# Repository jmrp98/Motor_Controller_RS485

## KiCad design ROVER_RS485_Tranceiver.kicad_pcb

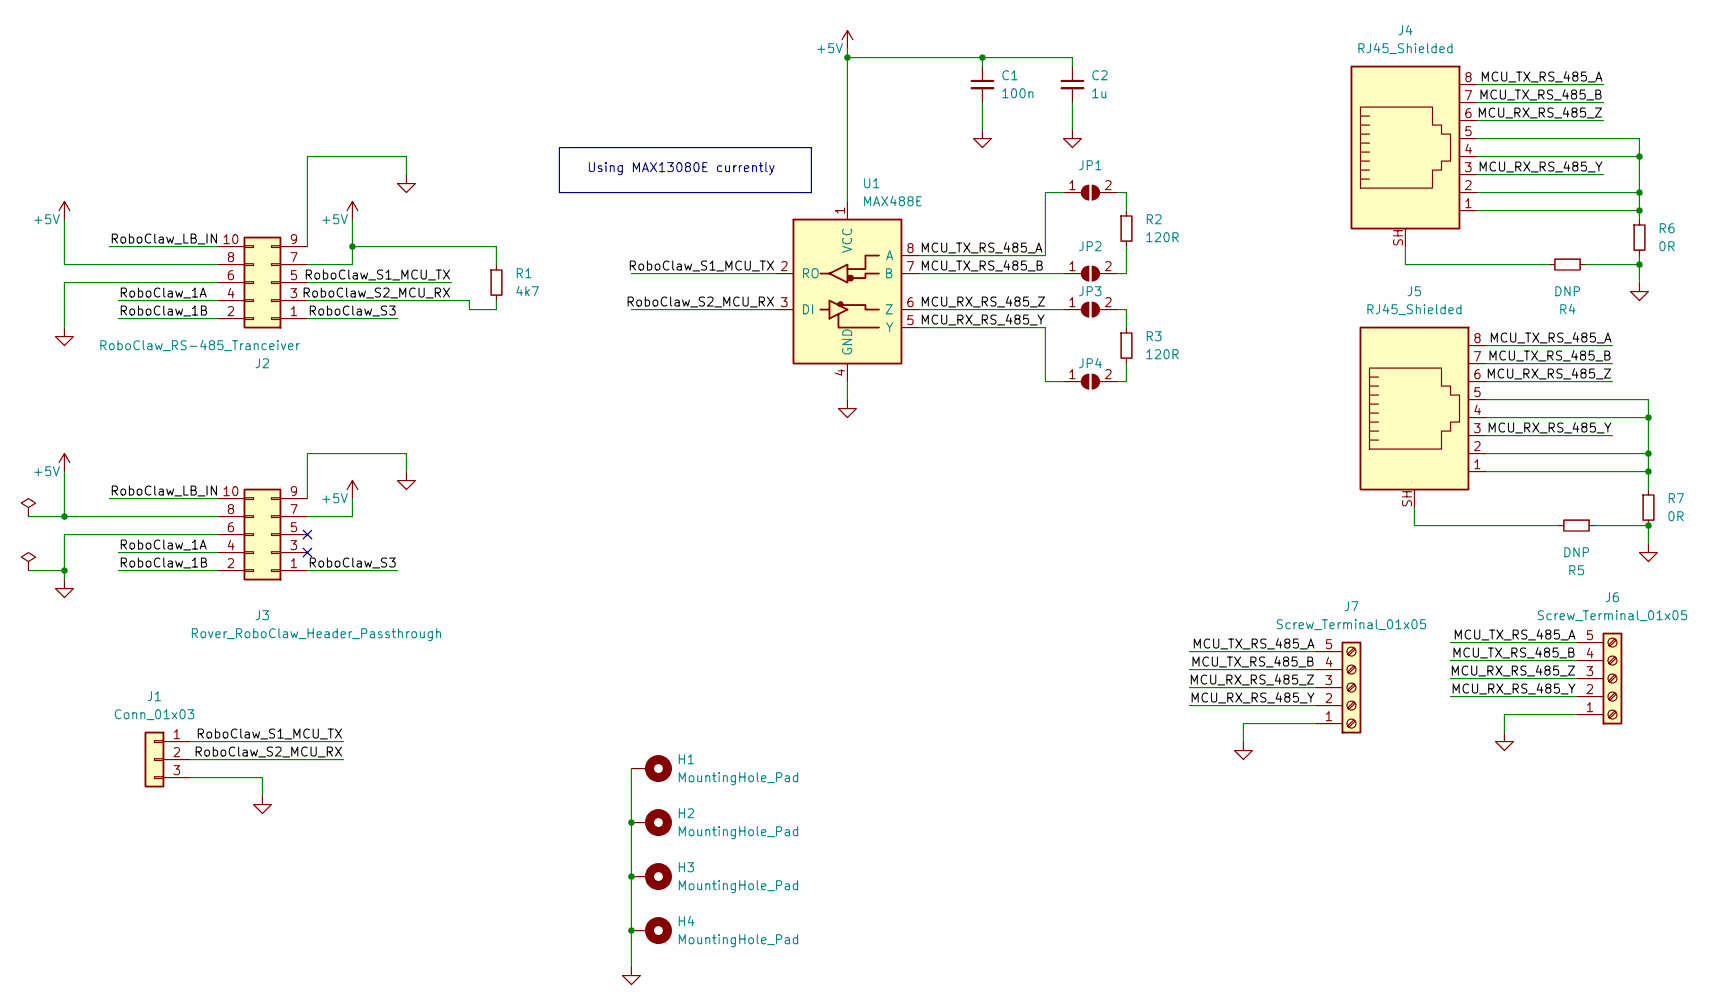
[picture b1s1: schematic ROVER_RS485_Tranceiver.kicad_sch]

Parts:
C1: 100n; C_0603_1608Metric
C2: 1u; C_0603_1608Metric
H1, H2, H3, H4: MountingHole_Pad; MountingHole_2.7mm_M2.5_DIN965_Pad
J1: Conn_01x03; PinHeader_1x03_P2.54mm_Vertical
J2: RoboClaw_RS-485_Tranceiver; PinSocket_2x05_P2.54mm_Horizontal
J3: Rover_RoboClaw_Header_Passthrough; PinHeader_2x05_P2.54mm_Horizontal
J4, J5: RJ45_Shielded; RJ45_Amphenol_RJHSE5380
J6, J7: Screw_Terminal_01x05; TerminalBlock_Phoenix_MPT-0,5-5-2.54_1x05_P2.54mm_Horizontal
JP1, JP2, JP3, JP4: SolderJumper_2_Open; SolderJumper-2_P1.3mm_Open_TrianglePad1.0x1.5mm
R1: 4k7; R_0603_1608Metric
R2, R3: 120R; R_0603_1608Metric
R4, R5: DNP; R_0603_1608Metric
R6, R7: 0R; R_0603_1608Metric
U1: MAX488E; SOIC-8_3.9x4.9mm_P1.27mm

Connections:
+5V: C1.1, C2.1, J2.7, J2.8, J3.7, J3.8, R1.1, U1.1 (VCC)
/MCU_RX_RS_485_Y: J4.3, J5.3, J6.2, J7.2, JP4.1 (A), U1.5 (Y)
/MCU_RX_RS_485_Z: J4.6, J5.6, J6.3, J7.3, JP3.1 (A), U1.6 (Z)
/MCU_TX_RS_485_A: J4.8, J5.8, J6.5, J7.5, JP1.1 (A), U1.8 (A)
/MCU_TX_RS_485_B: J4.7, J5.7, J6.4, J7.4, JP2.1 (A), U1.7 (B)
/RoboClaw_1A: J2.4, J3.4
/RoboClaw_1B: J2.2, J3.2
/RoboClaw_LB_IN: J2.10, J3.10
/RoboClaw_S1_MCU_TX: J1.1, J2.5, U1.2 (RO)
/RoboClaw_S2_MCU_RX: J1.2, J2.3, R1.2, U1.3 (DI)
/RoboClaw_S3: J2.1, J3.1
GND: C1.2, C2.2, H1.1, H2.1, H3.1, H4.1, J1.3, J2.6, J2.9, J3.6, J3.9, J6.1, J7.1, R4.1, R5.1, R6.2, R7.2, U1.4 (GND)
unnamed: J4.1, J4.2, J4.4, J4.5, R6.1
unnamed: J4.SH, R4.2
unnamed: J5.1, J5.2, J5.4, J5.5, R7.1
unnamed: J5.SH, R5.2
unnamed: JP1.2 (B), R2.1
unnamed: JP2.2 (B), R2.2
unnamed: JP3.2 (B), R3.1
unnamed: JP4.2 (B), R3.2

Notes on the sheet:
Using MAX13080E currently

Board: 2 copper layers, 25 parts (0 on the bottom side), 20 nets, no tracks yet.

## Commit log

2022-12-06 Initialize repo
